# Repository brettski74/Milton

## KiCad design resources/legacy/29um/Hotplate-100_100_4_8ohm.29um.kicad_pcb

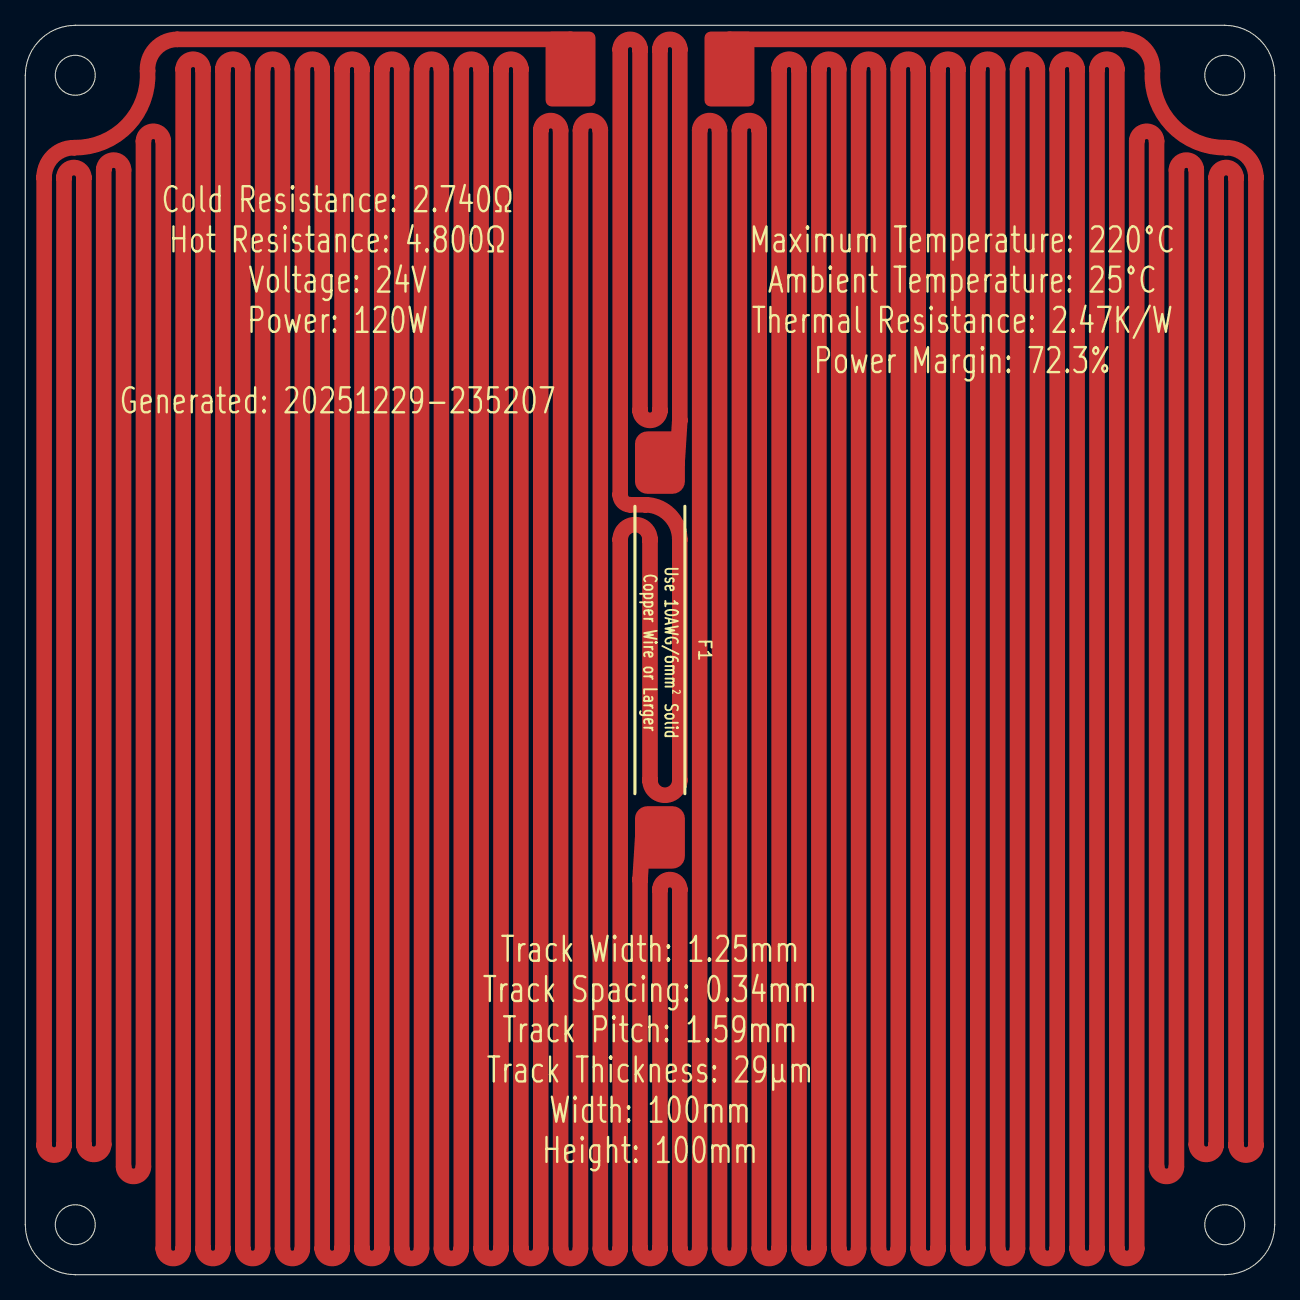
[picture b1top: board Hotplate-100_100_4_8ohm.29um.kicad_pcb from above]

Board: 2 copper layers, 100.0 x 100.0 mm, 3 parts (0 on the bottom side), 2 nets.

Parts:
F1: Thermal Fuse, SN100C, Front, 35mm
J1, J2: Hotplate_Power_Connection; SMD_PowerConnection_4x6mm

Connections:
unnamed: F1.1, J1.1
unnamed: F1.2, J2.1
